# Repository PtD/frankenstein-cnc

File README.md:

# frankenstein-cnc
Software and hardware to allow 3D printing and laser cutting/engraving from Mach3

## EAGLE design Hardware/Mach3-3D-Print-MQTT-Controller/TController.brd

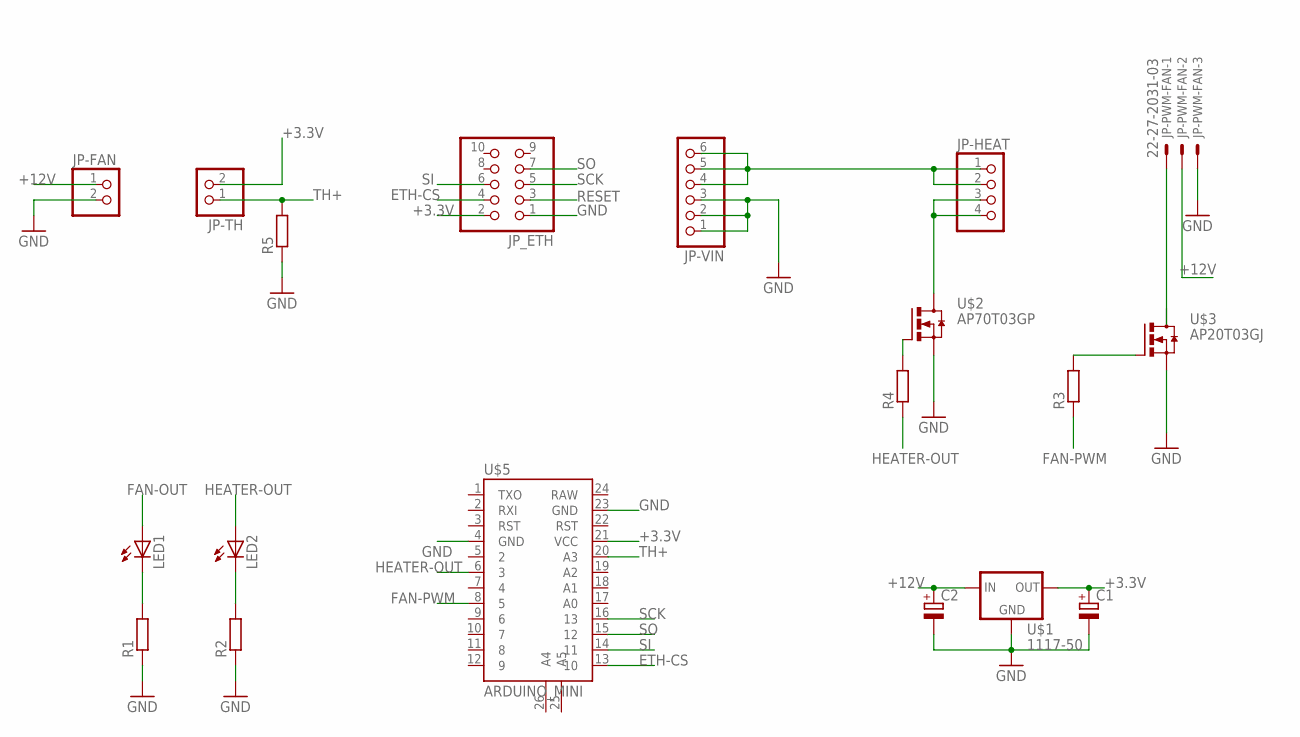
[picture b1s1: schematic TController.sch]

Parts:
C1, C2: CPOL-EUE2.5-6; E2,5-6
JP-FAN: PINHD-1X2; 1X02
JP-HEAT: PINHD-1X4; 1X04
JP-PWM-FAN: 22-27-2031-03; 6410-03
JP-TH: PINHD-1X2; 1X02
JP-VIN: PINHD-1X6; 1X06
JP_ETH: PINHD-2X5; 2X05
LED1, LED2: LED3MM
R1, R2, R3, R4, R5: R-EU_0207/10; 0207/10
U$1: 1117-50; SOT223
U$2: AP70T03GP; TO220V
U$3: AP20T03GJ; TO-251
U$5: ARDUINO_MINI

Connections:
+3.3V: C1.+, JP-TH.2, JP_ETH.2, U$1.2 (OUT), U$1.4 (OUT), U$5.21 (VCC)
+12V: C2.+, JP-FAN.1, JP-HEAT.1, JP-HEAT.2, JP-PWM-FAN.2, JP-VIN.4, JP-VIN.5, JP-VIN.6, U$1.3 (IN)
ETH-CS: JP_ETH.4, U$5.13 (10)
FAN-OUT: LED1.A
FAN-PWM: R3.1, U$5.8 (5)
GND: C1.-, C2.-, JP-FAN.2, JP-PWM-FAN.3, JP-VIN.1, JP-VIN.2, JP-VIN.3, JP_ETH.1, R1.1, R2.1, R5.1, U$1.1 (GND), U$2.3 (S), U$3.S, U$5.4 (GND), U$5.23 (GND)
HEATER-OUT: LED2.A, R4.1, U$5.6 (3)
unnamed: R3.2, U$3.G
unnamed: R4.2, U$2.1 (G)
unnamed: JP-PWM-FAN.1, U$3.D
unnamed: JP-HEAT.3, JP-HEAT.4, U$2.2 (D)
unnamed: LED1.K (C), R1.2
unnamed: LED2.K (C), R2.2
RESET: JP_ETH.3
SCK: JP_ETH.5, U$5.16 (13)
SI: JP_ETH.6, U$5.14 (11)
SO: JP_ETH.7, U$5.15 (12)
TH+: JP-TH.1, R5.2, U$5.20 (A3)

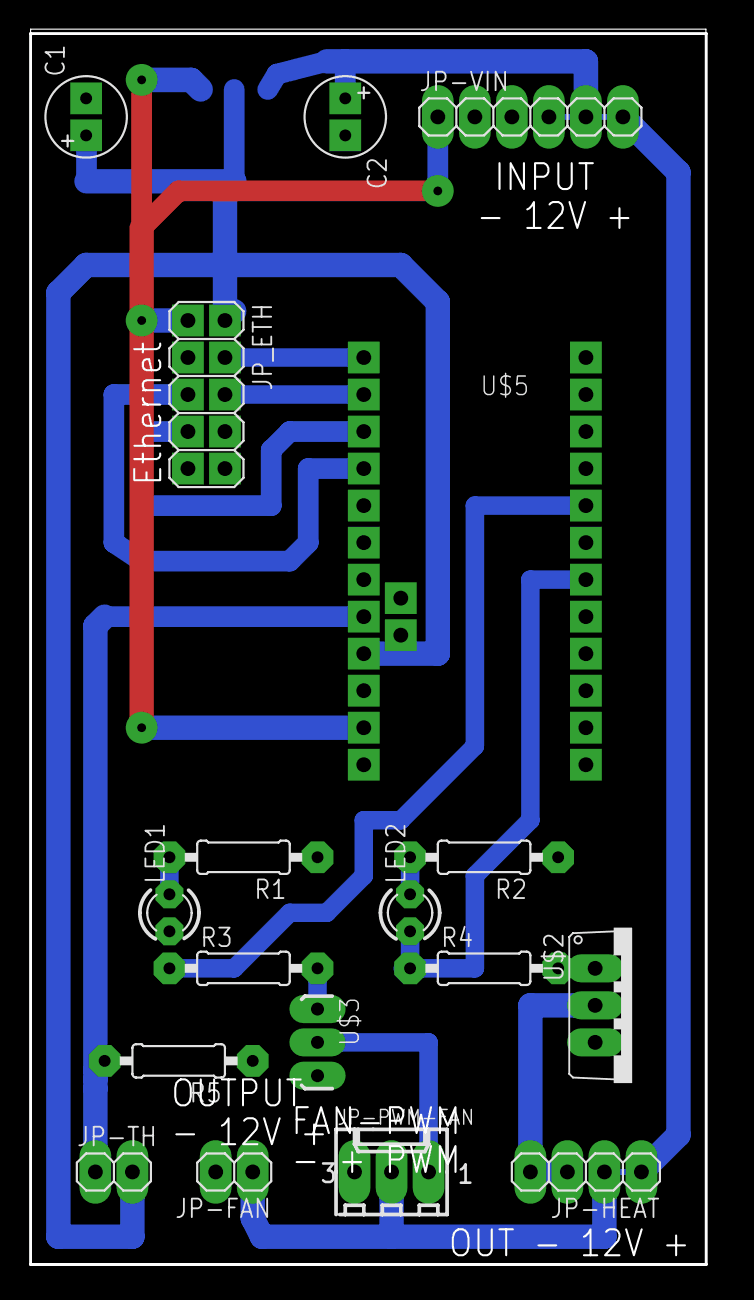
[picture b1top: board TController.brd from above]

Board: 2 copper layers, 47.5 x 85.0 mm, 19 parts (1 on the bottom side), 16 nets.

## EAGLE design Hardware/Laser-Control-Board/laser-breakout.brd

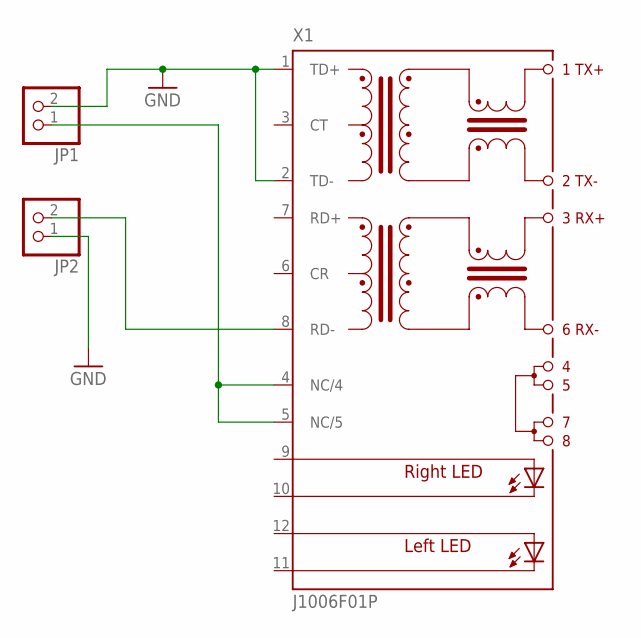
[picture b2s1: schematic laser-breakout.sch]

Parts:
JP1, JP2: PINHD-1X2; 1X02
X1: J1006F01P; J1

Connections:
12V: JP1.1, X1.4 (NC/4), X1.5 (NC/5)
GND: JP1.2, JP2.1, X1.1 (TD+), X1.2 (TD-)
TTL: JP2.2, X1.8 (RD-)

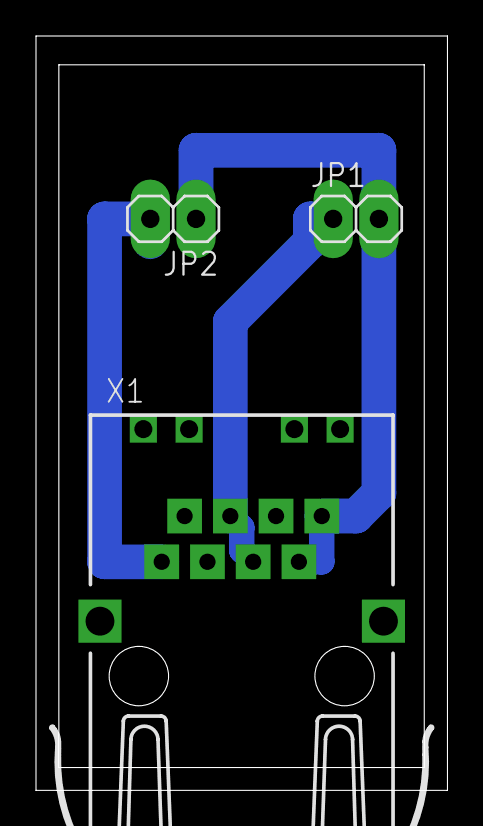
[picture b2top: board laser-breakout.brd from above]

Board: 2 copper layers, 22.9 x 41.9 mm, 3 parts (0 on the bottom side), 3 nets.

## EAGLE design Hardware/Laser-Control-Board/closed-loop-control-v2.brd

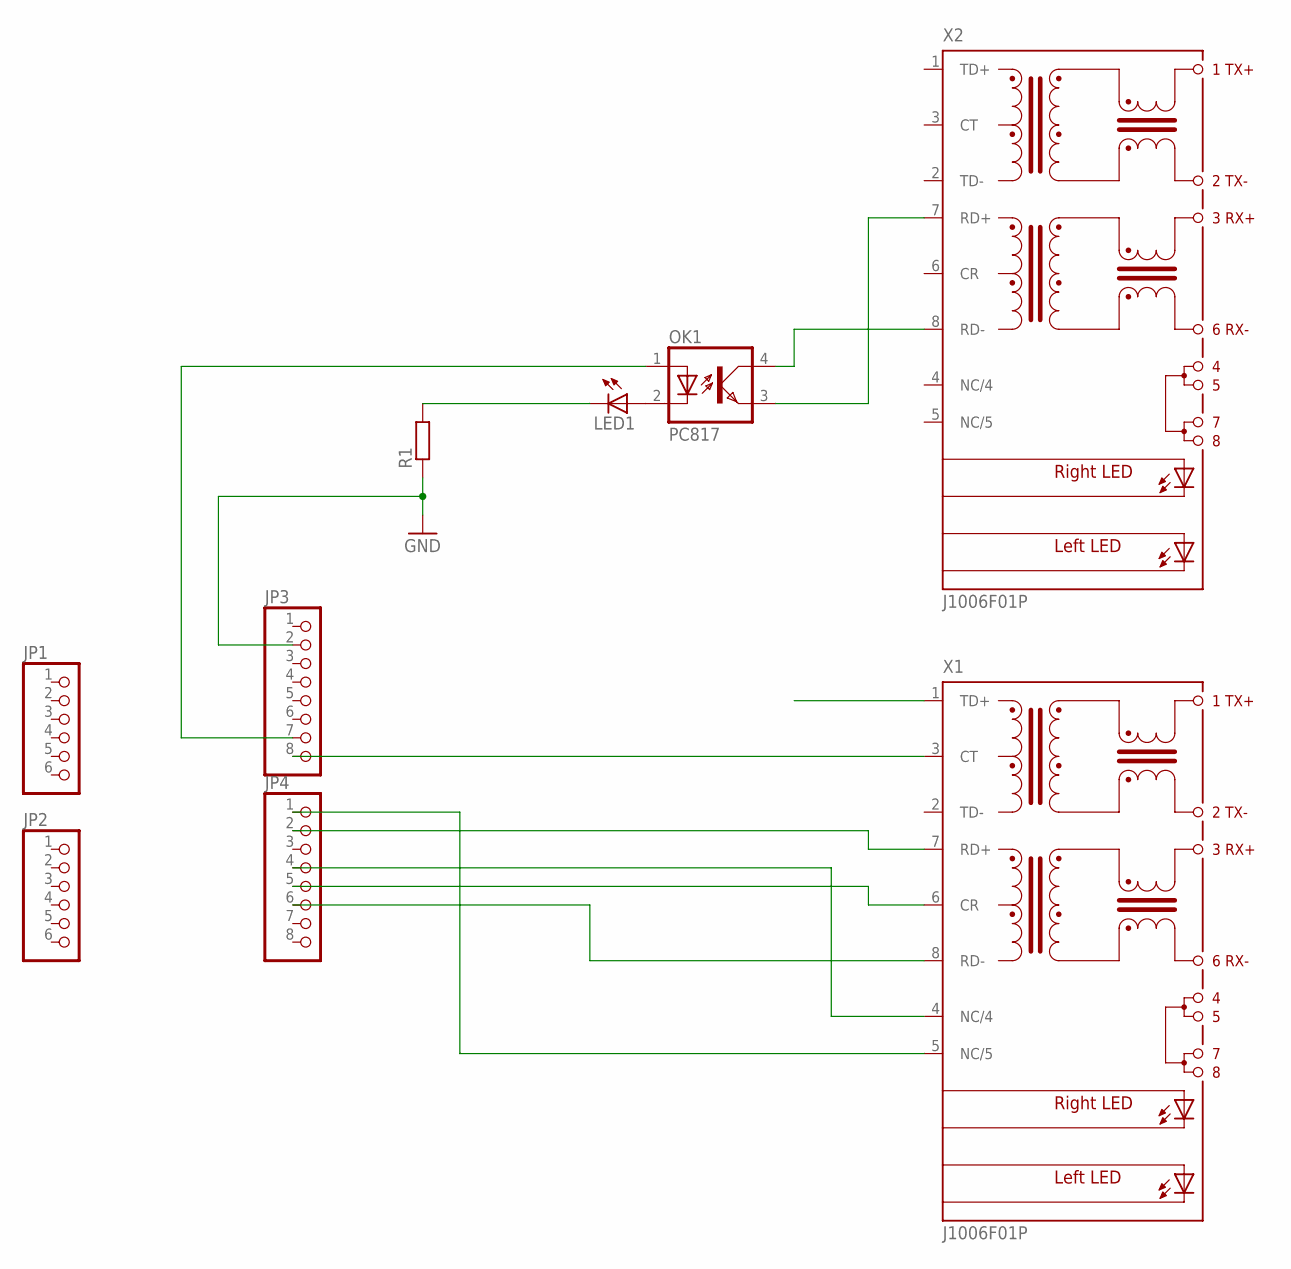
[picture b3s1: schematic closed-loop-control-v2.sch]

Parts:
JP1, JP2: PINHD-1X6; 1X06
JP3, JP4: PINHD-1X8; 1X08
LED1: LED3MM
OK1: PC817; DIL04
R1: R-EU_0207/10; 0207/10
X1, X2: J1006F01P; J1

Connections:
COUNT-X: JP4.6, X1.8 (RD-)
COUNT-Y: JP4.5, X1.6 (CR)
COUNT-Z: JP4.4, X1.4 (NC/4)
DIR-X: JP4.2, X1.7 (RD+)
DIR-Y: JP4.1, X1.5 (NC/5)
DIR-Z: JP3.8, X1.3 (CT)
GND: JP3.2, R1.1, X1.1 (TD+)
LASER-TTL: OK1.4 (COL), X2.8 (RD-)
LASER-TTL-CMD: JP3.7, OK1.1 (A)
LASER-TTL-GND: OK1.3 (EMIT), X2.7 (RD+)
unnamed: LED1.A, OK1.2 (C)
unnamed: LED1.K (C), R1.2

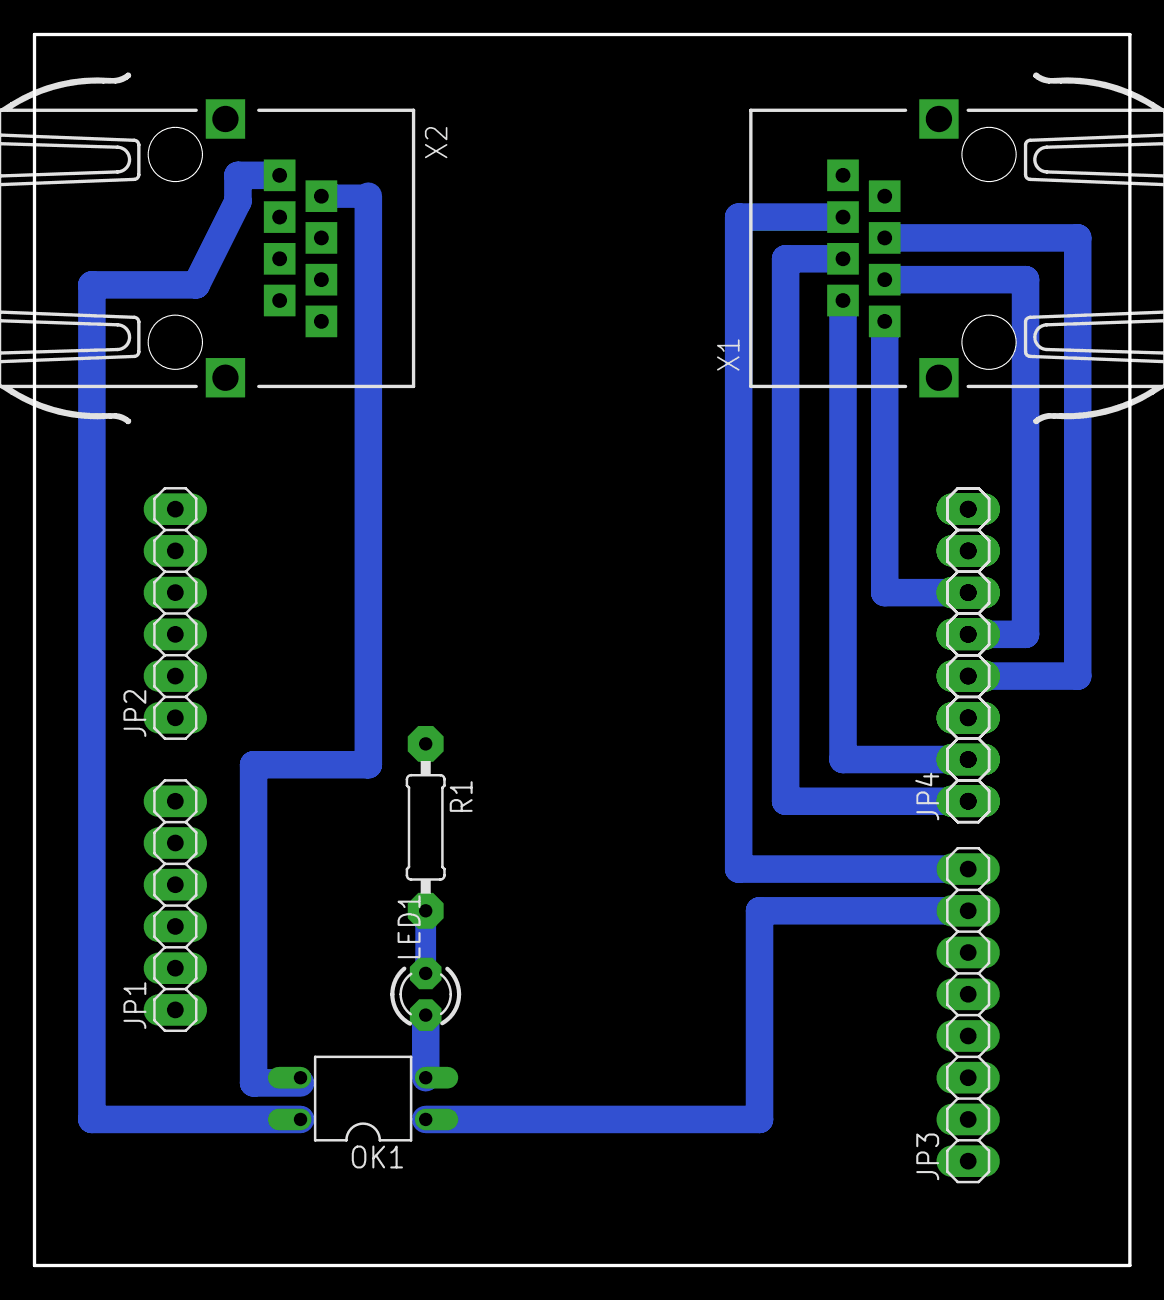
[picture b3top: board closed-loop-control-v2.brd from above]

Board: 2 copper layers, 66.7 x 74.9 mm, 10 parts (0 on the bottom side), 12 nets.

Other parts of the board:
IOL1: 1X08

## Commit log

2018-01-03 Initial submit
2018-01-04 Add more info
2018-01-04 Adding pcb schematics and board layouts
2018-01-06 Added support for disabling XYZ reporting
2018-01-06 Adding support for suppressing XYZ report (no more unnecessary network congestion!)
2018-01-07 Add back the Mach3 topic subscription Change default IP address of the laser controller Change MAC address of the laser controller
2018-01-08 Document Python Paho MQTT dependency
2018-01-08 Small UI layout adjustment
2018-01-10 Adding gitignore
2018-01-18 Rename temperature controller to match folder Update .gitignore
2019-10-26 Turn off laser when head is stationary
2019-10-28 Changing timing to prevent burnt dots at beginning/end of a trajectory
2019-11-01 Added support for dashed lines (M502P<count>) and reworked the laser turn on/turn off logic
2019-11-02 Laser control macros
2020-01-15 Fixed the read from configuration
